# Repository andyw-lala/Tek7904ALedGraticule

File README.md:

# Tek7904ALedGraticule
A project to retro-fit LED graticule lighting to Tektronix 7904A scopes.

Inspired by the white LED upgrade to a [Tek 7854 by Zenwizard Studios](https://youtu.be/GYkjuE7Pez8).

The 7904A is not so so straightforward that you can simply replace the lamps with LEDs and a series resistor.

This design replaces the existing incandescent graticule lamp driver circuit with a variable current source, all the existing controls are honoured, including intensity, gate and manual modes.

This upgrade is also featured at the beginning of Zenwizard Studios video: [Tektronix 7904A Lab Check in and LED MOD](https://youtu.be/GQn0EqW-u74).

## Theory of Operation
The 7904A controls the graticule illumination by means of circuitry on the A1 PCB (front panel board, located upper right front of scope.) This control circuit is documented on schematic 7 of my version of the manual (R1900, R1902, Q1910, S1905, S1910, etc.) Ultimately these various mechanisms result in a single -15V to 0V output signal on pin 4 of P1917; where -15V is illumination off, and 0V is full brighness.

This signal is then whisked off to the A22 PCB (LV Regulator board, located towards the rear.) The control signal is used by Q144, Q148 and associated components (schematic 15 in my version of the manual) to control a 0v to 6V output that is fed to the lamps via the A1 PCB again and a beefy pull-up resistor to +15V (R301.) The original lamps are wired in parallel, as shown on schematic 2.

The replacement re-uses all the control circuitry, so behaviour is identical, including all the modes and controls such as preset brightness, gated, and manual operation. However, it uses the -15V to 0V control voltage to control a 0 - 20mA current from the +15V rail through the replacement LEDs, which are wired in series. The circuit uses a simple emitter follower (T1) to convert the control voltage into a current sink, and a [Wilson current mirror](https://en.wikipedia.org/wiki/Wilson_current_mirror) (T2,3,4) to convert that into a current source to ground for the LEDs. It seemed apt, since George Wilson was a Tek engineer when he developed the eponymous circuit. The absolute accuracy of the mirror is not too important; so unmatched, discrete, transistors are used.

This is accomplished by inserting a small circuit with the additional electronics in the existing ribbon cable connection between the A1 and A22 boards. The control signal to, and the lamp power from, A22 are disconnected and no longer passed through. The pull-up resistor (R301 on A1) is removed.

The graticule light board (A30) is modified to replace the lamps with wide angle white LEDs,and to wire them in series.

## [Schematic](V3.pdf) (pdf)

## [BOM](BOM.md)

## Eagle Files
* [Schematic](V3.sch)
* [Board](V3.brd)

## Gerber Files
Here are generated gerbers, so you can use your PCB house of choice.
Note that I have only checked these with a viewer, I ordered my boards direct from OSHPark using the eagle board file. Send feedback if you use these files and the work or don't work.
* [Gerber zipfile](V3_gerbers.zip)

## Order Boards
You can order multiples of three known good boards directly from [OSHpark](https://oshpark.com/shared_projects/jouvs37V)

## Installation
There are four simple steps required in addition to making the circuit board (all obviously accomplished with the scope off, and fully discharged):
1. Reworking the graticule light board (A30.)
First remove the graticule lamp assembly from the scope, this is accomplished as follows:
    1. [Remove the plastic trim around the CRT](images/PXL_20220108_233952439.jpg), by gently pulling it away from the screen.
    2. [Loosen the two screws holding the retaining clips](images/PXL_20220108_234001968.jpg) for the tinted filter, and rotate the clips out of the way.
    3. Remove the tinted filter.
    4. [Remove the graticule light assembly](images/PXL_20220108_234047702.jpg) by gently pushing the white plastic clips inwards until [the assembly can be pulled forward](images/PXL_20220108_234137003.jpg). Be gentle, these clips can be brittle.
    5. Desolder the two wires that go to the PCB, taking note of which wire goes where in the PCB - in my case the green wire went to the trace marked "Ground", and the yellow wire went to the trace marked "+". Tape the wires to avoid them disappearing back inside the body of the scope and complicating the process.
    6. [Remove the PCB](images/PXL_20210615_022417282.jpg) from the clear plastic light guide.
    7. [Desolder lamps](images/PXL_20210615_022752127.jpg).
    8. [Pre-bend the LED leads](images/PXL_20210615_023820695.jpg).
    9. [Solder LEDs in place](images/PXL_20210615_024128291.jpg) - noting orientation.
    10. [Cut PCB traces](images/PXL_20210615_024433127.jpg) in three places, to convert from parallel to series wiring.
    11. [Add jumper wire as shown](images/PXL_20210615_024639665.jpg) to complete series wiring.
    12. Re-solder A30 PCB to wires on scope, observing the correct polarity.
    12. Re-assemble by reversing steps i - vi.
2. Remove [R301](images/R301-Location-1.jpg), the [300 Ohm, 1W resistor](images/R301-Location-2.jpg) on the A1 board. I did not bother desoldering it, and simply removed it by cutting the leads.
3. Mount the additional PCB. I bolted it to the horizontal rail running along the right hand side of the chassis, using one of the existing holes near the rear of the scope.
4. Remove the ribbon cable that is plugged into P17 on the Low Voltage Regulator board (A22), and [attach it to the additional PCB](images/PXL_20210720_014014225.jpg) in the location marked "To A1 P1917", paying attention to the orientation of pin 1. This is P1 on the schematic. Connect the location marked "To A22 P17" on the additional PCB (P2 on schematic) via additional ribbon cable to the now unused P17 on A22.
I was able to find a 5-way Tek cable that I pulled from some parts mule, and I used that to make the connection between A22 and the additional PCB. Obviously, other solutions are possible, such as cutting the existing ribbon cable and soldering it directly to the additional PCB.

# Licence
All work here is covered by the MIT Licence, which is simple and permissive.

# Disclaimer
This mod worked well for me, and is presented here in the hope it can be as useful to others. However, do not undertake this unless you have the skills to perform the work safely and without damaging anything. You perform all work at your own risk, and I have no responsibility for any damage or injury whatsoever.

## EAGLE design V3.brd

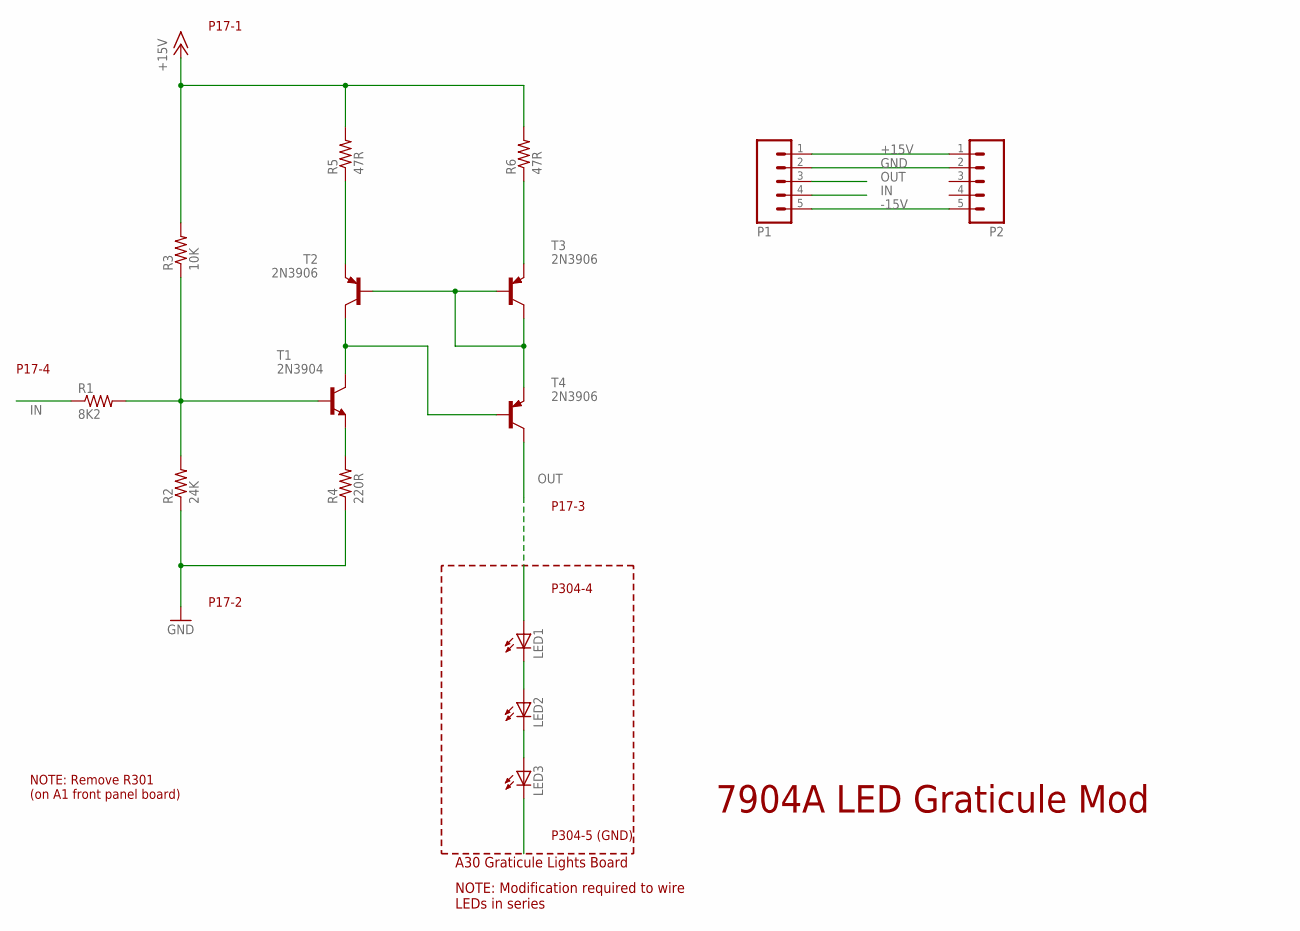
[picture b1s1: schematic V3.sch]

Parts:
LED1, LED2, LED3: LED5MM
P1, P2: M05PTH; 1X05
R1: 8K2; 0309/12
R2: 24K; 0309V
R3: 10K; 0309V
R4: 220R; 0309V
R5, R6: 47R; 0309V
T1: 2N3904; TO92-EBC
T2, T3, T4: 2N3906; TO92-EBC

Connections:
+15V: P1.1, P2.1, R3.2, R5.2, R6.2
-15V: P1.5, P2.5
GND: P1.2, P2.2, R2.1, R4.1
IN: P1.4, R1.1
unnamed: R1.2, R2.2, R3.1, T1.B
unnamed: R4.2, T1.E
unnamed: R5.1, T2.E
unnamed: LED2.K (C), LED3.A
unnamed: LED1.K (C), LED2.A
unnamed: R6.1, T3.E
unnamed: T2.B, T3.B, T3.C, T4.E
unnamed: T1.C, T2.C, T4.B
OUT: P1.3, T4.C

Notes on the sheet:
P304-5 (GND)
P304-4
P17-3
P17-4
NOTE: Remove R301 (on A1 front panel board)
7904A LED Graticule Mod
A30 Graticule Lights Board
NOTE: Modification required to wire LEDs in series
P17-1
P17-2

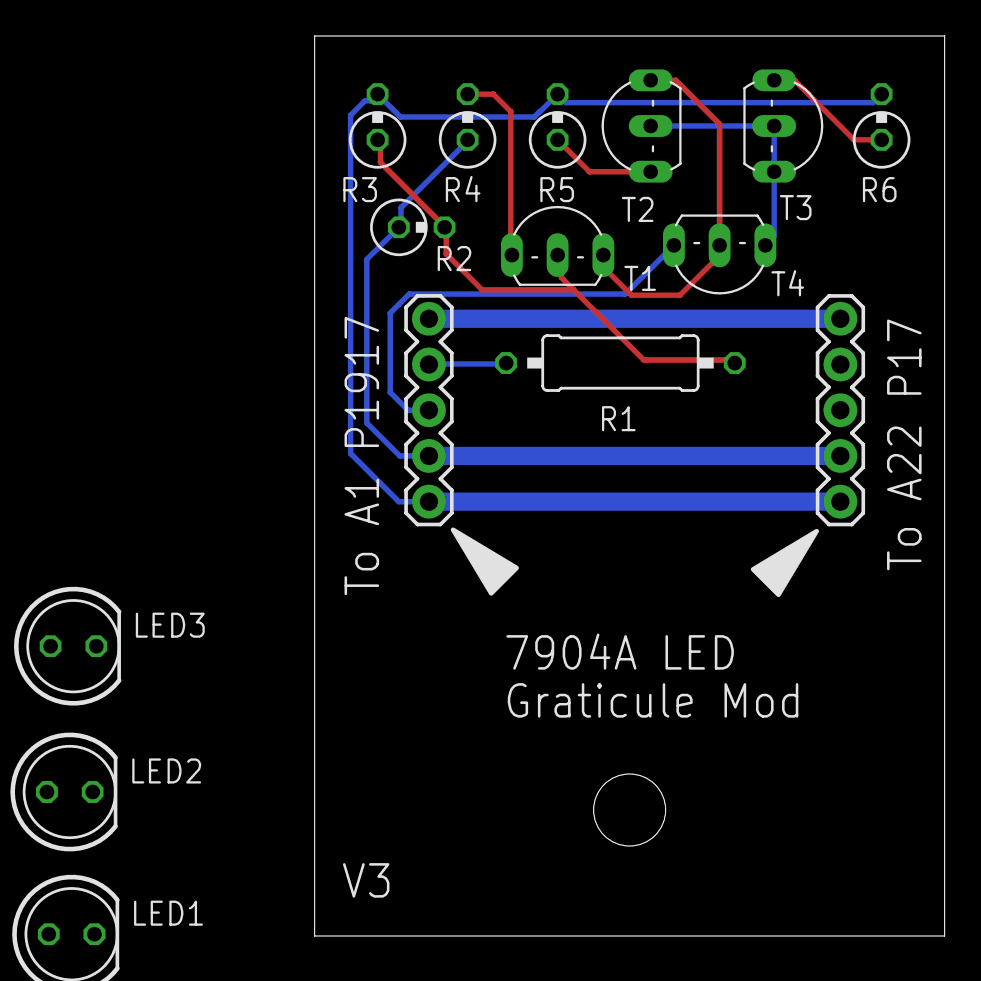
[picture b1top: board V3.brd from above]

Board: 2 copper layers, 35.0 x 50.0 mm, 15 parts (0 on the bottom side), 13 nets.

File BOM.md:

# BOM
Designator | Value | Description
----------------------
LED1 | C535A-WJN-CT0W0231 | 5mm Cool White LED, 110 degrees
LED2 | C535A-WJN-CT0W0231 | 5mm Cool White LED, 110 degrees
LED3 | C535A-WJN-CT0W0231 | 5mm Cool White LED, 110 degrees
P1 | | 5 pin 0.1" header
R1 | 8K2 | 1/4W 5%
R2 | 24K | 1/4W 5%
R3 | 10K | 1/4W 5%
R4 | 220R | 1/4W 5%
R5 | 47R | 1/4W 5%
R6 | 47R | 1/4W 5%
T1 | 2N3904 | NPN
T2 | 2N3906 | PNP
T3 | 2N2906 | PNP
T4 | 2N2906 | PNP

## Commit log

2021-07-29 Initial content.
2021-07-29 Initial checking of eagle files and schematic pdf.
2021-07-29 Add circuit description reminder.
2021-07-29 Add licence reminder.
2021-07-30 Add photo of 7904A screen after.
2021-07-30 Add picture to readme
2021-07-30 Schematic without pad layer.
2021-07-30 Add BOM.
2021-07-30 Fix table
2021-07-30 Add P2
2021-07-30 Tick items off todo list.
2021-07-30 Add pdf clarifier
2021-07-30 wizzle eagle file links.
2021-07-30 Lower case R
2021-07-30 Try and display schematic at top of BOM
2021-07-30 Show schematic png at top of BOM
2021-07-30 Clarify language
2021-08-03 Add disclaimer.
2022-01-09 Theory of operation, instructions, and photos.
2022-01-09 fix typos and move After.jpg into images directory.
2022-01-09 Keep installation step 4 together.
2022-01-09 Move V3.png to images directory.
2022-01-09 Minor tweaks to V3.png
2022-01-09 Link to images, swap steps 1.v and 1.vi, annotate PXL_20220108_234137003.jpg
2022-01-09 Remove last TODO
2022-01-09 Less repetition.
2022-01-09 Minor tweak.
2022-01-28 Add reference and link to youtube video featuring upgrade.
2022-01-28 Copy edit tweakage.
2022-02-01 Add gerbers.
2022-02-01 Typo

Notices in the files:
parts and their libraries:
SparkFun-Connectors: Licensing: Creative Commons ShareAlike 4.0 International - https://creativecommons.org/licenses/by-sa/4.0
